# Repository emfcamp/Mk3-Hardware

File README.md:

Hardware
========

Hardware for the TiLDA MKπ Badge for [Electromagnetic Field
2016](https://www.emfcamp.org).

Key Specs
---------
* [STM32L486VGT6](http://www.st.com/content/st_com/en/products/microcontrollers/stm32-32-bit-arm-cortex-mcus/stm32l4-series/stm32l4x6/stm32l486vg.html):
  80MHz ultra-low-power ARM Cortex M4 microcontroller. 1MB Flash, 128KB
  SRAM, USB2. Micropython compatible.
* [CC3100MOD](http://www.ti.com/product/CC3100MOD) SimpleLink WiFi
  Network Processor.
* [LSM6DS3](http://www.st.com/content/st_com/en/products/mems-and-sensors/inemo-inertial-modules/lsm6ds3.html)
  3D accelerometer/gyro.
* [LIS3MDL](http://www.st.com/content/st_com/en/products/mems-and-sensors/e-compasses/lis3mdl.html)
  3D magnetometer.

License
-------
Copyright Electromagnetic Field Ltd. 2016

This documentation describes Open Hardware and is licensed under the
CERN OHL v. 1.2.  You may redistribute and modify this documentation
under the terms of the CERN OHL v.1.2. (http://ohwr.org/cernohl or the
LICENSE file in this repository). This documentation is distributed
WITHOUT ANY EXPRESS OR IMPLIED WARRANTY, INCLUDING OF MERCHANTABILITY,
SATISFACTORY QUALITY AND FITNESS FOR A PARTICULAR PURPOSE. Please see
the CERN OHL v.1.2 for applicable conditions.

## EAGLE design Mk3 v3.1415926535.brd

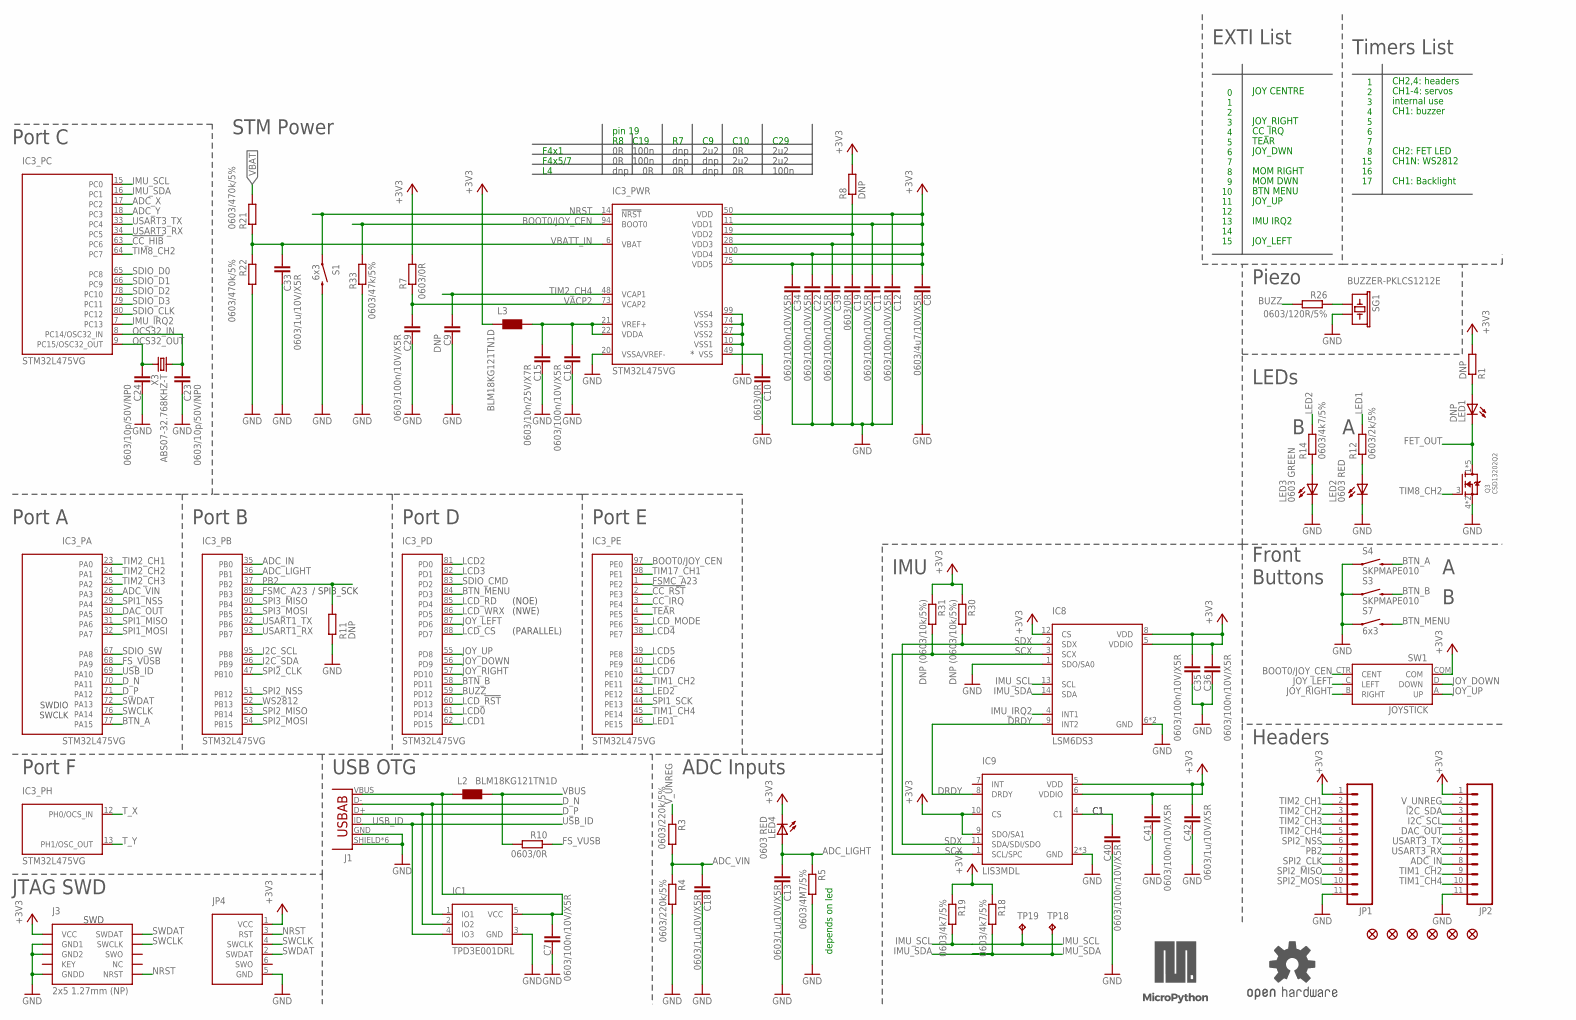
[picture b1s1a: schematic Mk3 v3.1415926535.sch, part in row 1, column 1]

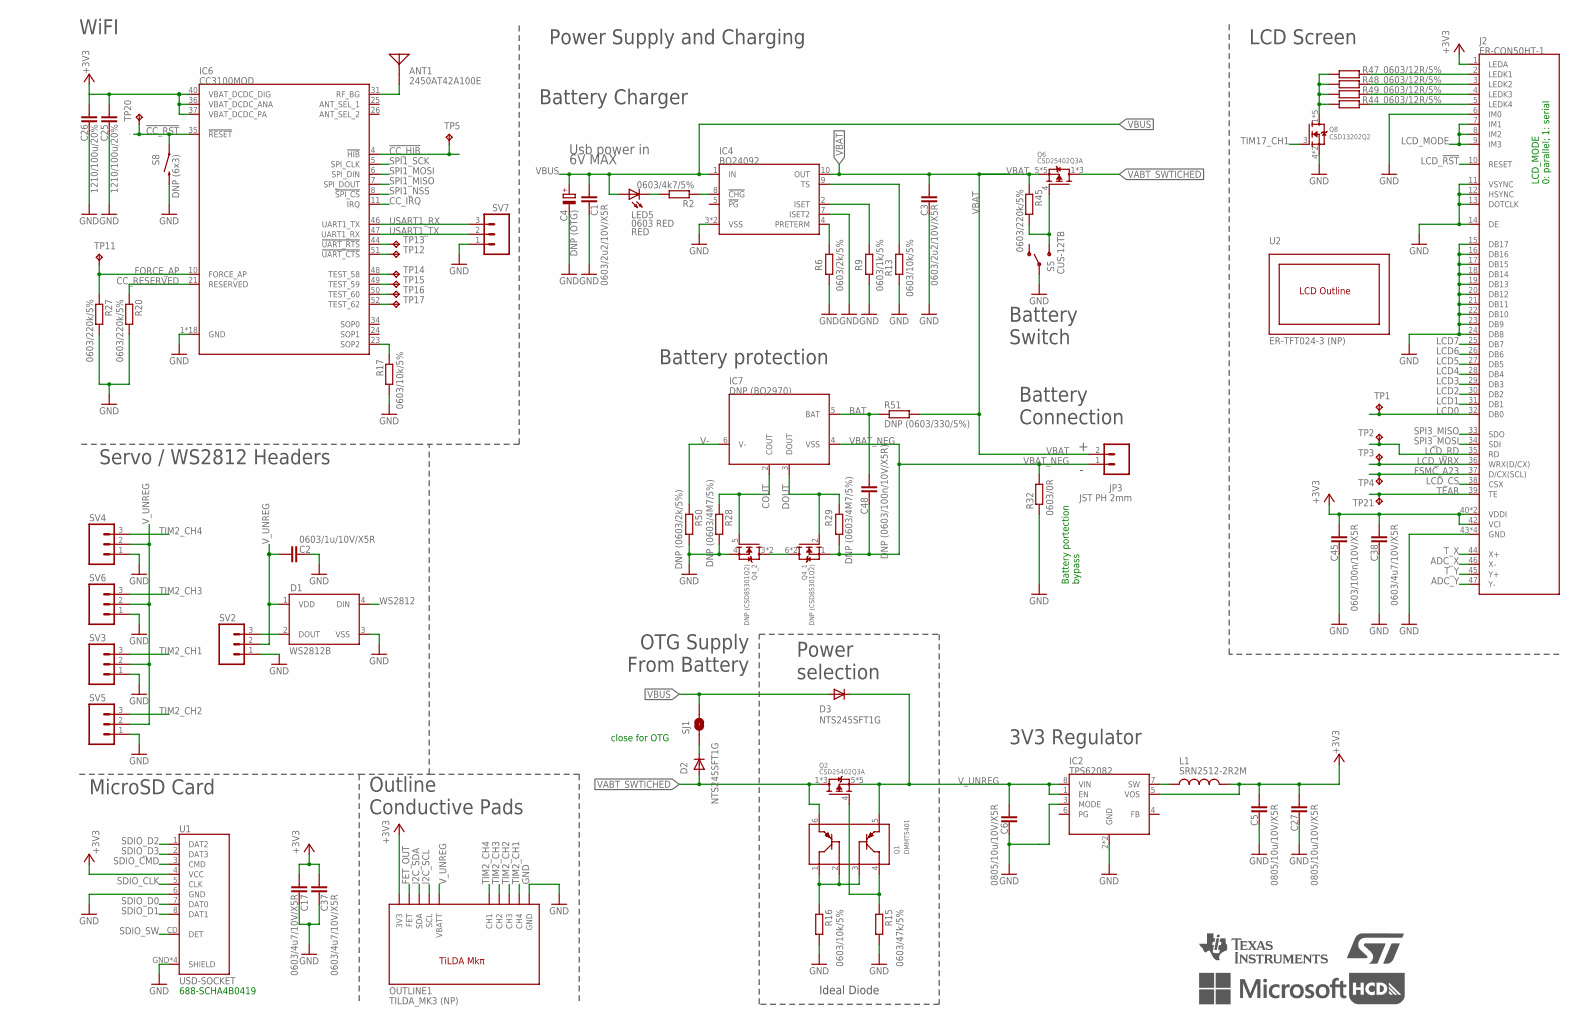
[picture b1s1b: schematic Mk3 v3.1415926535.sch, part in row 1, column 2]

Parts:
ANT1: 2450AT42A100E; 2450AT42A100; FARNELL 2148522
C1, C3: 0603/2u2/10V/X5R; C0603K-SMALL
C2, C13, C18, C33, C42: 0603/1u/10V/X5R; C0603K-SMALL
C4: DNP (OTG); E2,5-6
C5, C6, C27: 0805/10u/10V/X5R; C0805-N
C7, C11, C12, C16, C22, C29, C34, C35, C36, C39, C40, C41, C45: 0603/100n/10V/X5R; C0603K-SMALL
C8, C17, C37, C38: 0603/4u7/10V/X5R; C0603K-SMALL
C9: DNP; C0603K-SMALL
C10, C19: 0603/0R; C0603K-SMALL
C15: 0603/10n/25V/X7R; C0603K-SMALL
C23, C24: 0603/10p/50V/NP0; C0603K-SMALL
C25, C26: 1210/100u/20%; C1210K; FARNELL 1828817
C48: DNP (0603/100n/10V/X5R); C0603K-SMALL
D1: WS2812B
D2, D3: NTS245SFT1G; SOD123
FID1, FID2, FID3, FID4, FID5, FID6: FIDUCIAL1X2.5-STOP; FIDUCIAL-1X2.5-STOP
IC1: TPD3E001DRL; DRL-5; FARNELL 1603422
IC2: TPS62082; WSON8; FARNELL 2064227
IC3: STM32L475VG; TQFP100; FARNELL 2432116
IC4: BQ24092; HVSSOP10; FARNELL 2323723
IC6: CC3100MOD; CC3100MOD-LWK; MOUSER 595-3100MODR11MAMOBR
IC7: DNP (BQ2970); WSON-6; FARNELL 2425793
IC8: LSM6DS3; LGA14; FARNELL 2474253
IC9: LIS3MDL; LGA12; FARNELL 2433083
J1: ZX62-AB-5PA(11); USB-AB-MICRO-SMD_LWK; FARNELL 2293755
J2: ER-CON50HT-1; FH12-50S-0.5SH
J3: 2x5 1.27mm (NP); PINHEAD_2X05_127; FARNELL 1865285
JP1, JP2: (NP); 1X11
JP3: JST PH 2mm; JST-2-SMD; FARNELL 9492615
JP4: (NP); TC2030-MCP-NL
L1: SRN2512-2R2M; 1008; FARNELL 2428203
L2, L3: BLM18KG121TN1D; WUERTH-0805; FARNELL 1781089
LED1: DNP; LED5MM
LED2, LED4, LED5: 0603 RED; LED-0603-CORRECT; FARNELL 2449874
LED3: 0603 GREEN; LED-0603-CORRECT; FARNELL 2426215
LOGO1: OSHW-LOGOM (NP); OSHW-LOGO-M
LOGO2: LOGO_TI-4MM (NP); LOGO_TI_4MM
LOGO3: LOGO_ST-4MM (NP); LOGO_ST_4MM
LOGO4: LOGO_HCD-4MM (NP); LOGO_HDC_4MM
LOGO5: LOGO_MICROSOFT-4MM (NP); LOGO_MS_4MM
LOGO6: LOGO_MICROPYTHON-8MM (NP); LOGO_MICROPYTHON_8MM
OUTLINE1: TILDA_MK3 (NP); TILDA_MKE_OUTLINE
Q1: DMMT5401; SOT26; FARNELL 1773583
Q2, Q6: CSD25402Q3A; Q3A; FARNELL 2501103
Q3, Q8: CSD13202Q2; Q2; FARNELL 2501084
Q4: DNP (CSD85301Q2); Q2_DUAL; FARNELL 2470183
R1: DNP; 0207/10
R2, R14, R18, R19: 0603/4k7/5%; C0603K-SMALL
R3, R4, R20, R27, R45: 0603/220k/5%; C0603K-SMALL
R5: 0603/4M7/5%; C0603K-SMALL
R6, R12: 0603/2k/5%; C0603K-SMALL
R7, R10, R32: 0603/0R; C0603K-SMALL
R8, R11: DNP; C0603K-SMALL
R9: 0603/1k/5%; C0603K-SMALL
R13, R16, R17: 0603/10k/5%; C0603K-SMALL
R15, R33: 0603/47k/5%; C0603K-SMALL
R21, R22: 0603/470k/5%; C0603K-SMALL
R26: 0603/120R/5%; C0603K-SMALL
R28, R29: DNP (0603/4M7/5%); C0603K-SMALL; FARNELL 2059694
R30, R31: DNP (0603/10k/5%); C0603K-SMALL
R44, R47, R48, R49: 0603/12R/5%; C0603K-SMALL; FARNELL 9331280
R50: DNP (0603/2k/5%); C0603K-SMALL
R51: DNP (0603/330/5%); C0603K-SMALL
S1, S7: 6x3; TACTILE-SWITCH-1101NE
S3, S4: SKPMAPE010; SKPMAPE010-COMBINED; FARNELL 1217769
S5: CUS-12TB; SWITCH-SPST-SMD-A; FARNELL 9575146
S8: DNP (6x3); TACTILE-SWITCH-1101NE
SG1: BUZZER-PKLCS1212E
SJ1: OTG (NP); SJ_2S-NO
SV2, SV3, SV4, SV5, SV6, SV7: (NP); 1X03
SW1: JOYSTICK; JOYSTICK_MULTICOMP_NOSILK; FARNELL 1316987
TP1, TP2, TP3, TP4, TP5, TP11, TP12, TP13, TP14, TP15, TP16, TP17, TP18, TP19, TP20, TP21: (NP); B1,27
U1: USD-SOCKET; 0011XAAX09X; FARNELL 2427719
U2: ER-TFT024-3 (NP); ER-TFT024-3
X3: ABS07-32.768KHZ-T; RESONATOR_EPSON_FC_145; FARNELL 2101347

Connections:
!CC_HIB: IC3.63 (PC6), IC6.4 (!HIB), TP5.TP
!CC_RST: IC3.2 (PE3), IC6.35 (!RESET), S8.P$1 (1), TP20.TP
!UART_CTS: IC6.51 (!UART_CTS), TP12.TP
!UART_RTS: IC6.44 (!UART_RTS), TP13.TP
+3V3: C5.1, C8.2, C11.2, C12.2, C17.2, C22.2, C25.1, C26.1, C27.1, C34.2, C35.1, C36.1, C37.2, C38.2, C39.2, C41.1, C42.1, C45.2, IC2.5 (VOS), IC3.11 (VDD1), IC3.28 (VDD3), IC3.50 (VDD), IC3.75 (VDD5), IC3.100 (VDD4), IC6.36 (VBAT_DCDC_ANA), IC6.37 (VBAT_DCDC_PA), IC6.40 (VBAT_DCDC_DIG), IC8.5 (VDDIO), IC8.8 (VDD), IC8.12 (CS), IC9.5 (VDD), IC9.6 (VDDIO), IC9.9 (SDO/SA1), IC9.10 (CS), J2.1 (LEDA), J2.40 (VDDI), J2.41 (VDDI), J2.42 (VCI), J3.1 (VCC), JP1.1, JP2.1, JP4.1 (VCC), L1.2, L3.1, LED4.C, OUTLINE1.3V3, R1.2, R7.1, R8.2, R18.1, R19.1, R30.1, R31.1, SW1.COM, U1.4 (VCC)
ADC_IN: IC3.35 (PB0), JP2.8
ADC_LIGHT: C13.2, IC3.36 (PB1), LED4.A, R5.1
ADC_VIN: C18.2, IC3.26 (PA3), R3.2, R4.1
ADC_X: IC3.17 (PC2), J2.46 (X-)
ADC_Y: IC3.18 (PC3), J2.47 (Y-)
BAT: C48.2, IC7.5 (BAT), R51.1
BOOT0/JOY_CEN: IC3.94 (BOOT0), IC3.97 (PE0), R33.2, SW1.CTR (CENT)
BTN_A: IC3.77 (PA15), S4.2, S4.B1 (2), S4.B2 (2)
BTN_B: IC3.58 (PD11), S3.2, S3.B1 (2), S3.B2 (2)
BTN_MENU: IC3.84 (PD3), S7.P$2 (2)
BUZZ: IC3.59 (PD12), R26.2
C1: C40.1, IC9.4 (C1)
CC_IRQ: IC3.3 (PE4), IC6.11 (IRQ)
CC_RESERVED: IC6.21 (RESERVED), R20.1
COUT: IC7.2 (COUT), Q4.5 (G), R28.1
DAC_OUT: IC3.30 (PA5), JP2.5
DFGFDG: C15.2, C16.2, IC3.21 (VREF+), IC3.22 (VDDA), L3.2
DOUT: IC7.3 (DOUT), Q4.2 (G), R29.1
DRDY: IC8.9 (INT2), IC9.8 (DRDY)
D_N: IC1.1 (IO1), IC3.70 (PA11), J1.D-
D_P: IC1.2 (IO2), IC3.71 (PA12), J1.D+
FET_OUT: LED1.K (C), OUTLINE1.FET, Q3.1 (D), Q3.2 (D), Q3.5 (D), Q3.6 (D), Q3.EP1 (D)
FORCE_AP: IC6.10 (FORCE_AP), R27.1, TP11.TP
FSMC_A23: IC3.1 (PE2), IC3.89 (PB3), J2.37 (D/CX(SCL)), TP4.TP
FS_VUSB: IC3.68 (PA9), R10.1
GND: C1.1, C2.1, C3.1, C4.-, C5.2, C6.2, C7.1, C8.1, C9.1, C10.1, C11.1, C12.1, C13.1, C15.1, C16.1, C17.1, C18.1, C19.1, C22.1, C23.1, C24.1, C25.2, C26.2, C27.2, C29.1, C33.1, C34.1, C35.2, C36.2, C37.1, C38.1, C39.1, C40.2, C41.2, C42.2, C45.1, D1.3 (VSS), IC1.3 (GND), IC2.2 (GND), IC2.3 (MODE), IC2.EP (GND), IC3.10 (VSS1), IC3.20 (VSSA/VREF-), IC3.27 (VSS2), IC3.74 (VSS3), IC3.99 (VSS4), IC4.3 (VSS), IC4.7 (ISET2), IC4.EP (VSS), IC6.1 (GND), IC6.2 (GND), IC6.16 (GND), IC6.27 (GND), IC6.28 (GND), IC6.30 (GND), IC6.32 (GND), IC6.38 (GND), IC6.43 (GND), IC6.55 (GND), IC6.56 (GND), IC6.57 (GND), IC6.58 (GND), IC6.59 (GND), IC6.60 (GND), IC6.61 (GND), IC6.62 (GND), IC6.63 (GND), IC8.1 (SDO/SA0), IC8.6 (GND), IC8.7 (GND), IC9.2 (GND), IC9.3 (GND), IC9.12 (GND), J1.GND, J1.SHIELD, J1.SHIELD@0 (SHIELD), J1.SHIELD@1 (SHIELD), J1.SHIELD@2 (SHIELD), J1.SHIELD@3 (SHIELD), J1.SHIELD@5 (SHIELD), J2.6 (IM0), J2.11 (VSYNC), J2.12 (HSYNC), J2.13 (DOTCLK), J2.14 (DE), J2.15 (DB17), J2.16 (DB16), J2.17 (DB15), J2.18 (DB14), J2.19 (DB13), J2.20 (DB12), J2.21 (DB11), J2.22 (DB10), J2.23 (DB9), J2.24 (DB8), J2.43 (GND), J2.48 (GND), J2.49 (GND), J2.50 (GND), J3.3 (GND1), J3.5 (GND2), J3.9 (GNDD), JP1.11, JP2.11, JP4.5 (GND), LED2.C, LED3.C, OUTLINE1.GND, Q3.4 (S), Q3.EP2 (S), Q4.4 (S), Q8.4 (S), Q8.EP2 (S), R4.2, R5.2, R6.2, R9.2, R11.1, R13.2, R15.2, R16.2, R17.2, R20.2, R22.2, R27.2, R28.2, R32.1, R33.1, R50.2, S1.P$2 (2), S3.1, S3.A1 (1), S3.A2 (1), S4.1, S4.A1 (1), S4.A2 (1), S5.2, S7.P$1 (1), S8.P$2 (2), SG1.P$2 (2), SV2.1, SV3.1, SV4.1, SV5.1, SV6.1, SV7.1, U1.6 (GND), U1.GND (SHIELD), U1.GND1 (SHIELD), U1.GND2 (SHIELD), U1.GND3 (SHIELD)
I2C_SCL: IC3.95 (PB8), JP2.4, OUTLINE1.SCL
I2C_SDA: IC3.96 (PB9), JP2.3, OUTLINE1.SDA
IMU_IRQ2: IC3.7 (PC13), IC8.4 (INT1)
IMU_SCL: IC3.15 (PC0), IC8.13 (SCL), R19.2, TP19.TP
IMU_SDA: IC3.16 (PC1), IC8.14 (SDA), R18.2, TP18.TP
JOY_DOWN: IC3.56 (PD9), SW1.D (DOWN)
JOY_LEFT: IC3.87 (PD6), SW1.C (LEFT)
JOY_RIGHT: IC3.57 (PD10), SW1.B (RIGHT)
JOY_UP: IC3.55 (PD8), SW1.A (UP)
LCD0: IC3.61 (PD14), J2.32 (DB0), TP1.TP
LCD1: IC3.62 (PD15), J2.31 (DB1)
LCD2: IC3.81 (PD0), J2.30 (DB2)
LCD3: IC3.82 (PD1), J2.29 (DB3)
LCD4: IC3.38 (PE7), J2.28 (DB4)
LCD5: IC3.39 (PE8), J2.27 (DB5)
LCD6: IC3.40 (PE9), J2.26 (DB6)
LCD7: IC3.41 (PE10), J2.25 (DB7)
LCD_!RST: IC3.60 (PD13), J2.10 (RESET)
LCD_CS: IC3.88 (PD7), J2.38 (CSX)
LCD_MODE: IC3.5 (PE6), J2.7 (IM1), J2.8 (IM2), J2.9 (IM3)
LCD_RD: IC3.85 (PD4), J2.35 (RD), TP2.TP
LCD_WRX: IC3.86 (PD5), J2.36 (WRX(D/CX)), TP3.TP
LED1: IC3.46 (PE15), R12.2
LED2: IC3.43 (PE12), R14.2
LEDK1: J2.2 (LEDK1), R47.2
LEDK2: J2.3 (LEDK2), R48.2
LEDK3: J2.4 (LEDK3), R49.2
LEDK4: J2.5 (LEDK4), R44.2
unnamed: Q4.3 (D), Q4.6 (D), Q4.EP1 (D), Q4.EP2 (D)
unnamed: R26.1, SG1.P$1 (1)
unnamed: C19.2, IC3.19 (VDD2), R8.1
unnamed: Q1.4 (C2), Q2.4 (G), R15.1
unnamed: Q1.1 (C1), Q1.2 (B1), Q1.3 (B2), R16.1
unnamed: LED5.C, R2.2
unnamed: IC4.8 (!CHG), R2.1
unnamed: IC4.4 (PRETERM), R6.1
unnamed: IC4.2 (ISET), R9.1
unnamed: IC4.9 (TS), R13.1
unnamed: D1.2 (DOUT), SV2.3
unnamed: C7.2, IC1.5 (VCC), J1.VBUS, L2.1
unnamed: D2.C, SJ1.1
unnamed: ANT1.P$1, IC6.31 (RF_BG)
unnamed: C10.2, IC3.49 (VSS)
unnamed: LED3.A, R14.1
unnamed: LED2.A, R12.1
unnamed: LED1.A, R1.1
unnamed: Q8.1 (D), Q8.2 (D), Q8.5 (D), Q8.6 (D), Q8.EP1 (D), R44.1, R47.1, R48.1, R49.1
NRST: IC3.14 (!NRST), J3.10 (NRST), JP4.3 (RST), S1.P$1 (1)
OCS32_IN: C23.2, IC3.8 (PC14/OSC32_IN), X3.P$1 (1)
OCS32_OUT: C24.2, IC3.9 (PC15/OSC32_OUT), X3.P$2 (2)
PB2: IC3.37 (PB2), JP1.7, R11.2
SCX: IC8.3 (SCX), IC9.1 (SCL/SPC), R31.2
SDIO_CLK: IC3.80 (PC12), U1.5 (CLK)
SDIO_CMD: IC3.83 (PD2), U1.3 (CMD)
SDIO_D0: IC3.65 (PC8), U1.7 (DAT0)
SDIO_D1: IC3.66 (PC9), U1.8 (DAT1)
SDIO_D2: IC3.78 (PC10), U1.1 (DAT2)
SDIO_D3: IC3.79 (PC11), U1.2 (DAT3)
SDIO_SW: IC3.67 (PA8), U1.CD (DET)
SDX: IC8.2 (SDX), IC9.11 (SDA/SDI/SDO), R30.2
SOP2: IC6.23 (SOP2), R17.1
SPI1_MISO: IC3.31 (PA6), IC6.7 (SPI_DOUT)
SPI1_MOSI: IC3.32 (PA7), IC6.6 (SPI_DIN)
SPI1_NSS: IC3.29 (PA4), IC6.8 (!SPI_CS)
SPI1_SCK: IC3.44 (PE13), IC6.5 (SPI_CLK)
SPI2_CLK: IC3.47 (PB10), JP1.8
SPI2_MISO: IC3.53 (PB14), JP1.9
SPI2_MOSI: IC3.54 (PB15), JP1.10
SPI2_NSS: IC3.51 (PB12), JP1.6
SPI3_MISO: IC3.90 (PB4), J2.33 (SDO)
SPI3_MOSI: IC3.91 (PB5), J2.34 (SDI)
SW: IC2.7 (SW), L1.1
SWCLK: IC3.76 (PA14), J3.4 (SWCLK), JP4.4 (SWCLK)
SWDAT: IC3.72 (PA13), J3.2 (SWDAT), JP4.2 (SWDAT)
TEAR: IC3.4 (PE5), J2.39 (TE), TP21.TP
TEST_58: IC6.48 (TEST_58), TP14.TP
TEST_59: IC6.49 (TEST_59), TP15.TP
TEST_60: IC6.50 (TEST_60), TP16.TP
TEST_62: IC6.52 (TEST_62), TP17.TP
TIM1_CH2: IC3.42 (PE11), JP2.9
TIM1_CH4: IC3.45 (PE14), JP2.10
TIM2_CH1: IC3.23 (PA0), JP1.2, OUTLINE1.CH4, SV3.3
TIM2_CH2: IC3.24 (PA1), JP1.3, OUTLINE1.CH3, SV5.3
TIM2_CH3: IC3.25 (PA2), JP1.4, OUTLINE1.CH2, SV6.3
TIM2_CH4: C9.2, IC3.48 (VCAP1), JP1.5, OUTLINE1.CH1, SV4.3
TIM8_CH2: IC3.64 (PC7), Q3.3 (G)
TIM17_CH1: IC3.98 (PE1), Q8.3 (G)
T_X: IC3.12 (PH0/OCS_IN), J2.44 (X+)
T_Y: IC3.13 (PH1/OSC_OUT), J2.45 (Y+)
USART1_RX: IC3.93 (PB7), IC6.46 (UART1_TX), SV7.3
USART1_TX: IC3.92 (PB6), IC6.47 (UART1_RX), SV7.2
USART3_RX: IC3.34 (PC5), JP2.7
USART3_TX: IC3.33 (PC4), JP2.6
USB_ID: IC1.4 (IO3), IC3.69 (PA10), J1.ID (USBID)
V-: IC7.6 (V-), R50.1
VABT_SWTICHED: D2.A, Q1.6 (E1), Q2.1 (D), Q2.2 (D), Q2.3 (D), Q6.1 (D), Q6.2 (D), Q6.3 (D)
VACP2: C29.2, IC3.73 (VCAP2), R7.2
VBAT: C3.2, IC4.10 (OUT), JP3.2, Q6.5 (S), Q6.6 (S), Q6.7 (S), Q6.8 (S), Q6.EP (S), R21.2, R45.1, R51.2
VBATT_IN: C33.2, IC3.6 (VBAT), R21.1, R22.1
VBAT_NEG: C48.1, IC7.4 (VSS), JP3.1, Q4.1 (S), R29.2, R32.2
VBAT_SWITCH_CONTROL: Q6.4 (G), R45.2, S5.3 (S)
VBUS: C1.2, C4.+, D3.A, IC4.1 (IN), L2.2, LED5.A, R10.2, SJ1.2
V_UNREG: C2.2, C6.1, D1.1 (VDD), D3.C, IC2.1 (EN), IC2.8 (VIN), JP2.2, OUTLINE1.VBATT, Q1.5 (E2), Q2.5 (S), Q2.6 (S), Q2.7 (S), Q2.8 (S), Q2.EP (S), R3.1, SV2.2, SV3.2, SV4.2, SV5.2, SV6.2
WS2812: D1.4 (DIN), IC3.52 (PB13)

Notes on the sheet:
Headers
LCD Screen
STM Power
Port F
JTAG SWD
Port A
Port B
Port C
Port D
close for OTG
depends on led
MicroSD Card
Servo / WS2812 Headers
Port E
USB OTG
Battery Charger
LEDs
ADC Inputs
LCD_MODE 0: parallel; 1: serial
(PARALLEL)
(NOE)
(NWE)
688-SCHA4B0419
F4x1
F4x5/7
C19
pin 19
dnp
100n
2u2
C10
EXTI List
0 1 2 3 4 5 6 7 8 9 10 11 12 13 14 15
JOY CENTRE
TEAR
JOY_RIGHT
CC_IRQ
JOY_DWN
MOM RIGHT
MOM DWN

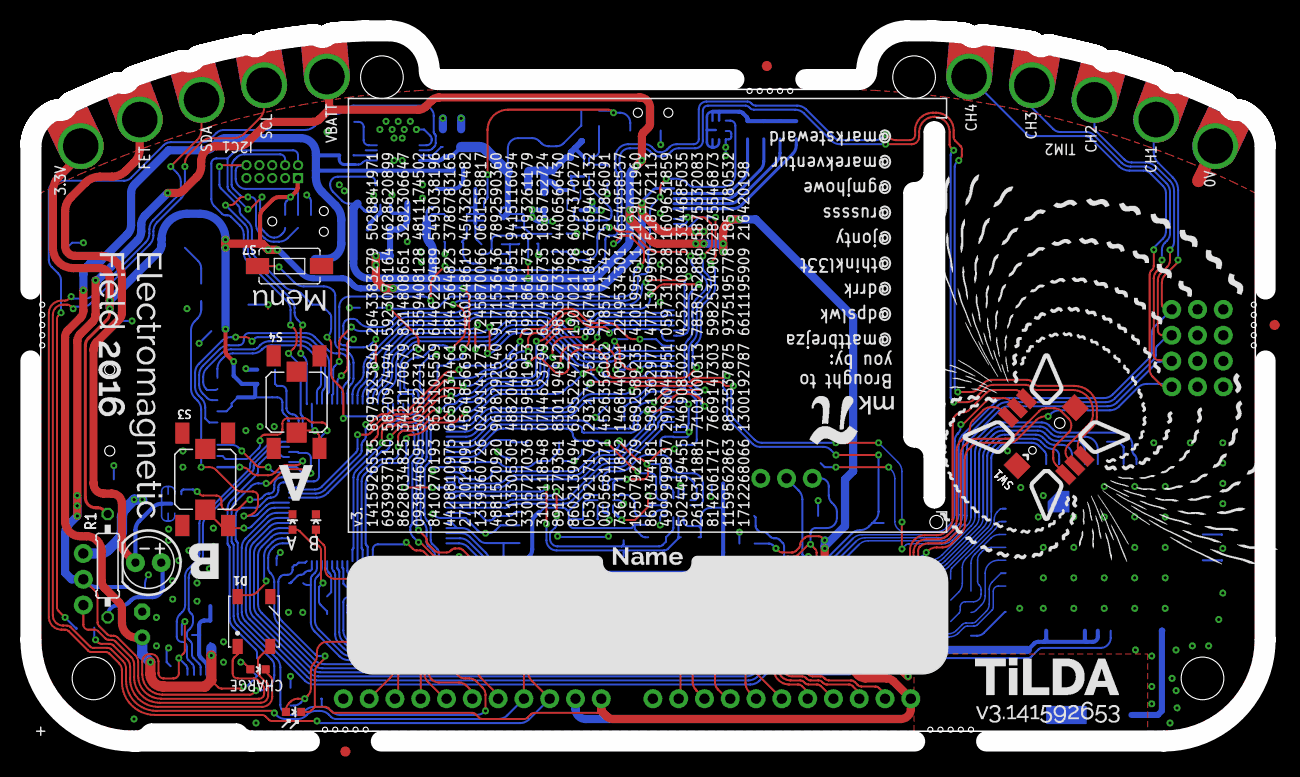
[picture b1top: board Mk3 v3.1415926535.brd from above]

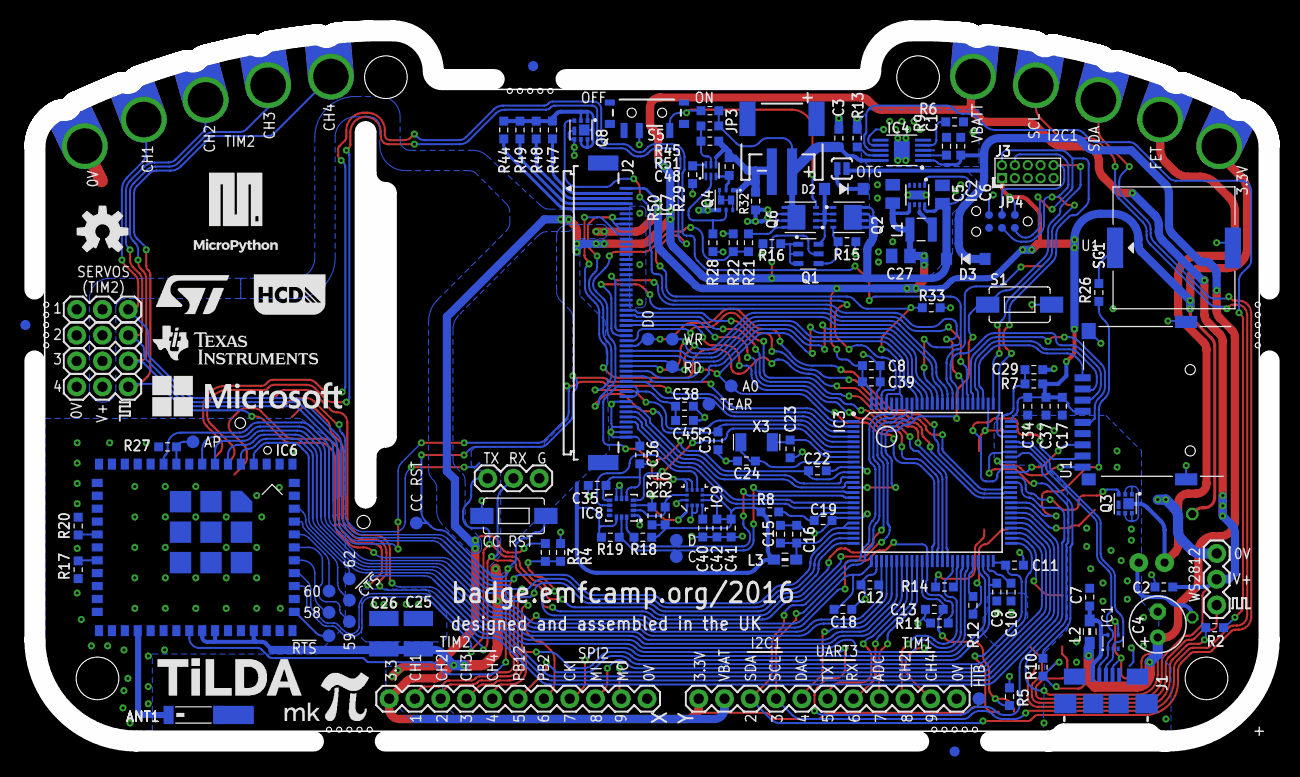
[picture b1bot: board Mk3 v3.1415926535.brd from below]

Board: 2 copper layers, 121.6 x 70.0 mm, 156 parts (139 on the bottom side), 135 nets.

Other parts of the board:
ARTWORK1: ARTWORK_MKπ_BACK; TILDA_MKπ_ARTWORK_BACK
ARTWORK2: ARTWORK_MKπ_FRONT; TILDA_MKπ_ARTWORK_FRONT

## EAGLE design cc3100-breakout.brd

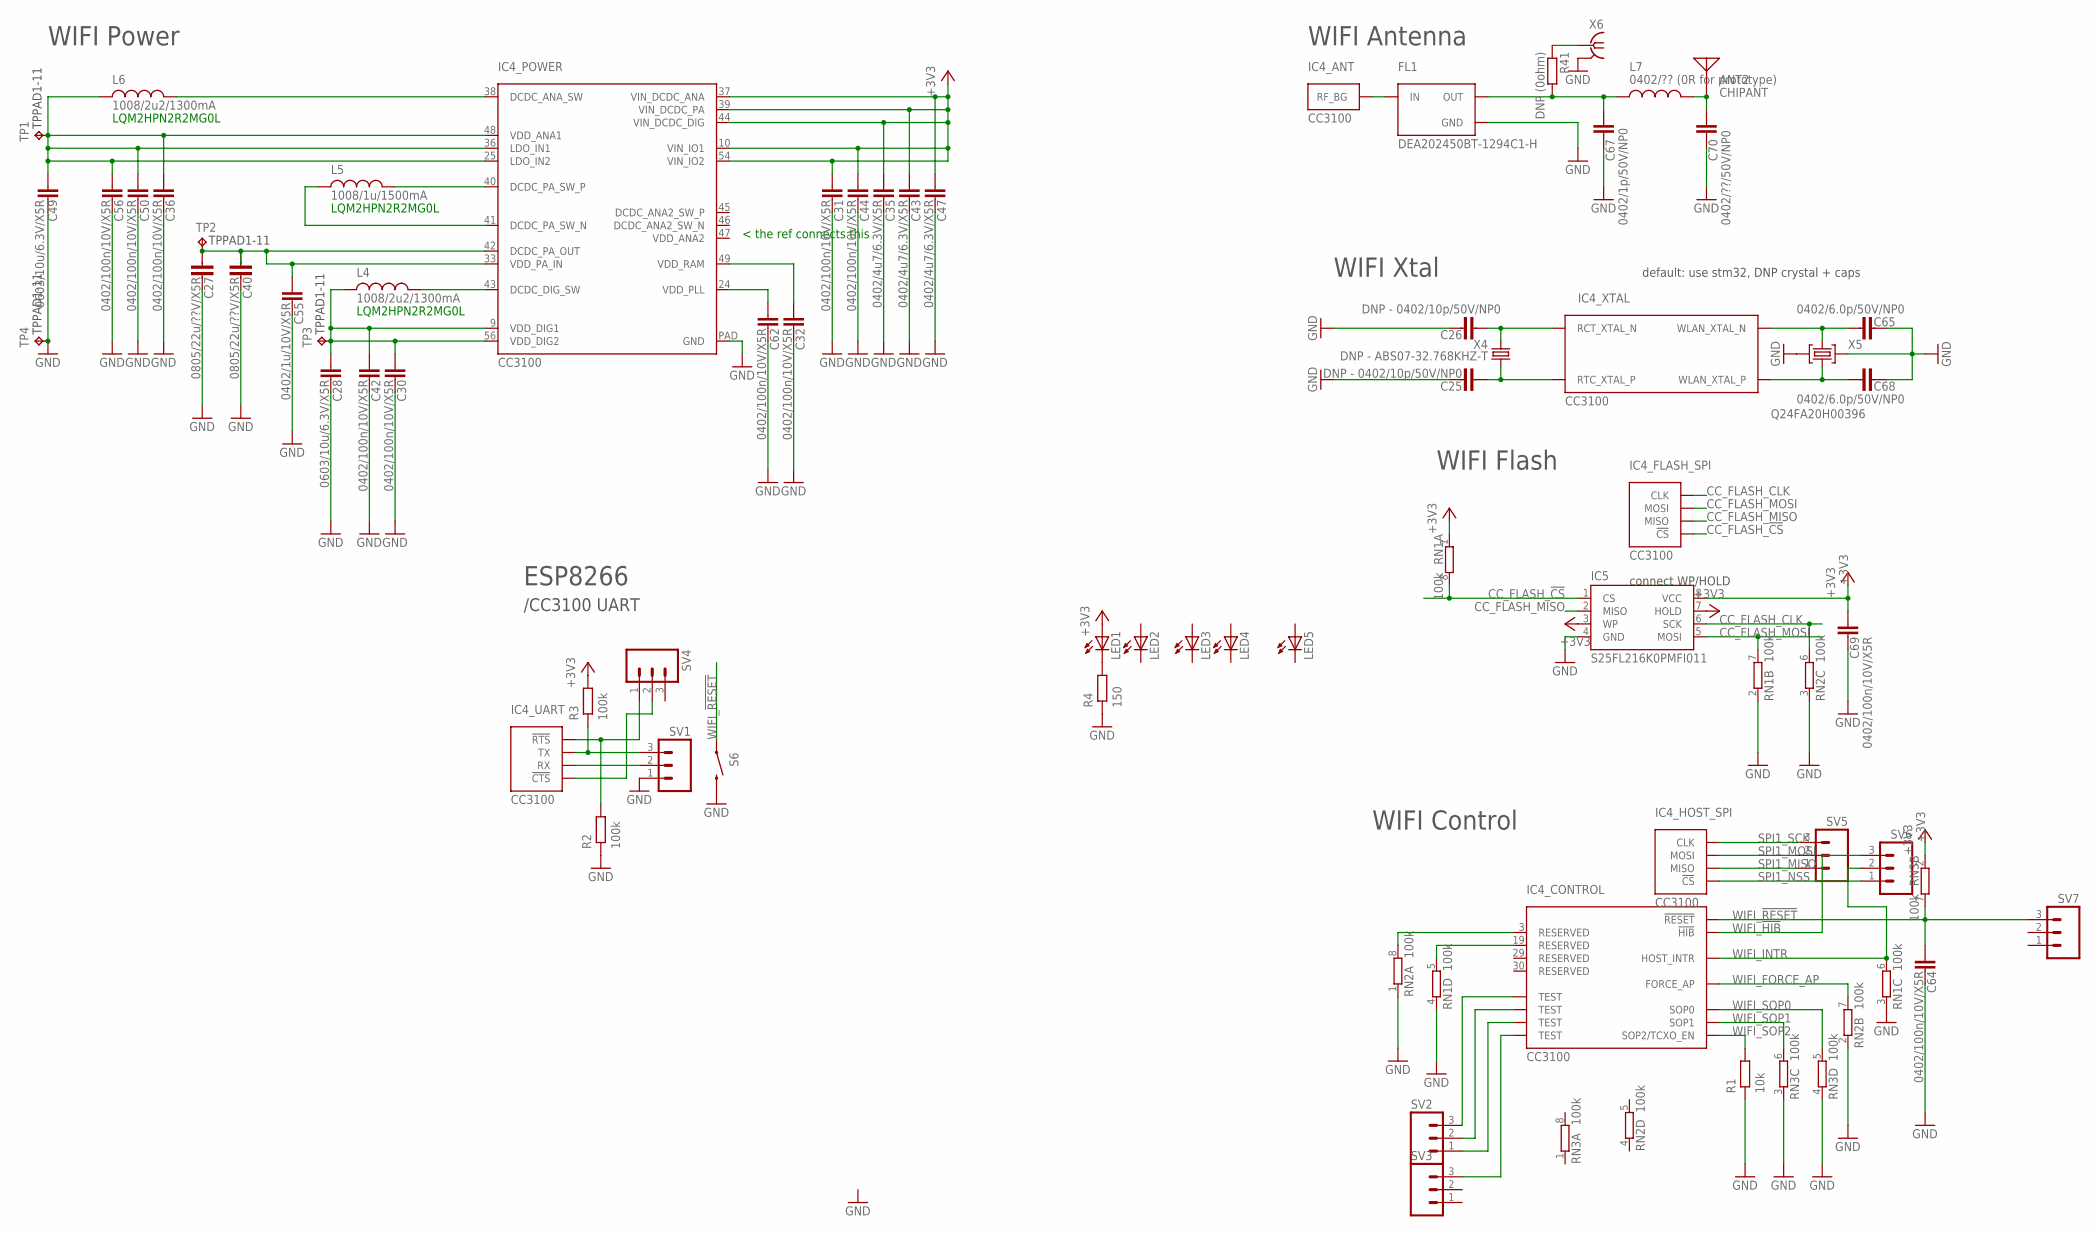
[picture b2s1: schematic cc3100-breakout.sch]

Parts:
ANT2: CHIPANT; 2450AT42A100
C25, C26: DNP - 0402/10p/50V/NP0; C0603-N
C27, C40: 0805/22u/??V/X5R; C0805-N
C28, C49: 0603/10u/6.3V/X5R; C0603K-SMALL
C30, C31, C32, C36, C42, C44, C50, C56, C62, C64, C69: 0402/100n/10V/X5R; C0402-SMALLER
C35, C43, C47: 0402/4u7/6.3V/X5R; C0402-SMALLER
C55: 0402/1u/10V/X5R; C0402-SMALLER
C65, C68: 0402/6.0p/50V/NP0; C0603-N
C67: 0402/1p/50V/NP0; C0402-SMALLER
C70: 0402/??/50V/NP0; C0402-SMALLER
FL1: DEA202450BT-1294C1-H; DEA202450BT
IC4: CC3100; VQFN-64
IC5: S25FL216K0PMFI011; SO08-EIAJ
L4, L6: 1008/2u2/1300mA; 1008
L5: 1008/1u/1500mA; 1008
L7: 0402/?? (0R for prototype); L0402
LED1, LED2, LED3, LED4, LED5: LEDCHIPLED_0603; CHIPLED_0603
R1: 10k; R0603-N
R2, R3: 100k; R0603-N
R4: 150; R0603-N
R41: DNP (0ohm); R0402-SMALLER
RN1, RN2, RN3: 100k; EXB38V
S6: SWITCH-MOMENTARY-2SMD-1101NE; TACTILE-SWITCH-1101NE
SV1, SV2, SV3, SV4, SV5, SV6, SV7: M03PTH; 1X03
TP1, TP2, TP3, TP4: TPPAD1-11; P1-11
X4: DNP - ABS07-32.768KHZ-T; RESONATOR_EPSON_FC_145
X5: Q24FA20H00396; CRYSTAL-2.5X2.0
X6: MC-921

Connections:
+3V3: C31.2, C35.2, C43.2, C44.2, C47.2, C69.2, IC4.10 (VIN_IO1), IC4.37 (VIN_DCDC_ANA), IC4.39 (VIN_DCDC_PA), IC4.44 (VIN_DCDC_DIG), IC4.54 (VIN_IO2), IC5.3 (WP), IC5.7 (HOLD), IC5.8 (VCC), LED1.A, R3.2, RN1.1, RN3.2 (1)
ANT: ANT2.P$1, C70.1, L7.2
CC_FLASH_!CS: IC4.14 (!CS), IC5.1 (CS), RN1.8 (2)
CC_FLASH_CLK: IC4.11 (CLK), IC5.6 (SCK), RN2.6 (2)
CC_FLASH_MISO: IC4.13 (MISO), IC5.2 (MISO)
CC_FLASH_MOSI: IC4.12 (MOSI), IC5.5 (MOSI), RN1.7 (2)
GND: C25.1, C26.1, C27.1, C28.1, C30.1, C31.1, C32.1, C35.1, C36.1, C40.1, C42.1, C43.1, C44.1, C47.1, C49.1, C50.1, C55.1, C56.1, C62.1, C64.1, C65.1, C67.2, C68.1, C69.1, C70.2, FL1.GND@2 (GND), FL1.GND@4 (GND), IC4.PAD (GND), IC5.4 (GND), R1.1, R2.1, R4.1, RN1.2 (1), RN1.3 (1), RN1.4 (1), RN2.1, RN2.2 (1), RN2.3 (1), RN3.3 (1), RN3.4 (1), S6.2, SV1.1, TP4.TP, X5.2 (GND), X5.4 (GND), X6.2@1 (GND), X6.2@2 (GND)
unnamed: IC4.50 (!RTS), R2.2, SV4.1
unnamed: C67.1, FL1.OUT, L7.1, R41.2
unnamed: FL1.IN, IC4.31 (RF_BG)
unnamed: IC4.58 (TEST), SV2.3
unnamed: C26.2, IC4.52 (RCT_XTAL_N), X4.P$1 (1)
unnamed: IC4.59 (TEST), SV2.2
unnamed: IC4.60 (TEST), SV2.1
unnamed: C65.2, IC4.22 (WLAN_XTAL_N), X5.3 (C2)
unnamed: C68.2, IC4.23 (WLAN_XTAL_P), X5.1 (C1)
unnamed: IC4.3 (RESERVED), RN2.8 (2)
unnamed: IC4.19 (RESERVED), RN1.5 (2)
unnamed: IC4.62 (TEST), SV3.3
unnamed: IC4.61 (!CTS), SV4.2
unnamed: LED1.C, R4.2
unnamed: IC4.38 (DCDC_ANA_SW), L6.2
unnamed: C27.2, C40.2, C55.2, IC4.33 (VDD_PA_IN), IC4.42 (DCDC_PA_OUT), TP2.TP
unnamed: C36.2, C49.2, C50.2, C56.2, IC4.25 (LDO_IN2), IC4.36 (LDO_IN1), IC4.48 (VDD_ANA1), L6.1, TP1.TP
unnamed: IC4.43 (DCDC_DIG_SW), L4.2
unnamed: C62.2, IC4.24 (VDD_PLL)
unnamed: C28.2, C30.2, C42.2, IC4.9 (VDD_DIG1), IC4.56 (VDD_DIG2), L4.1, TP3.TP
unnamed: IC4.40 (DCDC_PA_SW_P), L5.2
unnamed: IC4.41 (DCDC_PA_SW_N), L5.1
unnamed: C32.2, IC4.49 (VDD_RAM)
unnamed: C25.2, IC4.51 (RTC_XTAL_P), X4.P$2 (2)
unnamed: IC4.55 (TX), R3.1, SV1.3
unnamed: R41.1, X6.1
SPI1_MISO: IC4.7 (MISO), SV5.1
SPI1_MOSI: IC4.6 (MOSI), SV5.2
SPI1_NSS: IC4.8 (!CS), SV6.1
SPI1_SCK: IC4.5 (CLK), SV5.3
USART6_TX: IC4.57 (RX), SV1.2
WIFI_!HIB: IC4.2 (!HIB), SV6.3
WIFI_!RESET: C64.2, IC4.32 (!RESET), RN3.7 (2), S6.1, SV7.3
WIFI_FORCE_AP: IC4.4 (FORCE_AP), RN2.7 (2)
WIFI_INTR: IC4.15 (HOST_INTR), RN1.6 (2), SV6.2
WIFI_SOP0: IC4.35 (SOP0), RN3.5 (2)
WIFI_SOP1: IC4.34 (SOP1), RN3.6 (2)
WIFI_SOP2: IC4.21 (SOP2/TCXO_EN), R1.2

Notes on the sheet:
WIFI Antenna
WIFI Flash
WIFI Xtal
LQM2HPN2R2MG0L
WIFI Power
WIFI Control
default: use stm32, DNP crystal + caps
connect WP/HOLD
ESP8266
/CC3100 UART
< the ref connects this

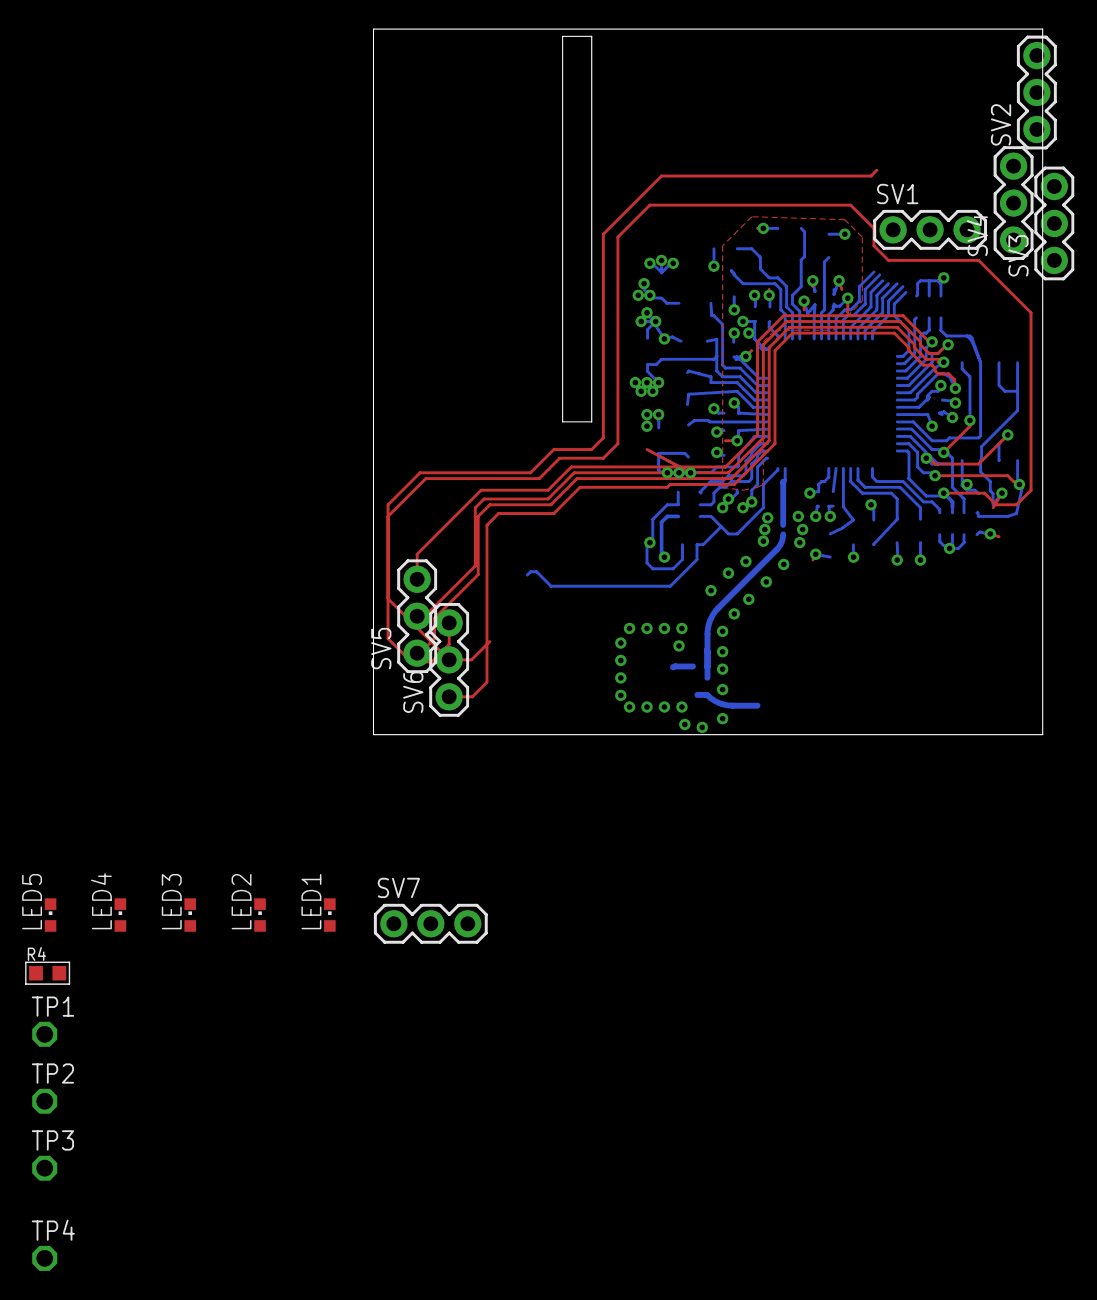
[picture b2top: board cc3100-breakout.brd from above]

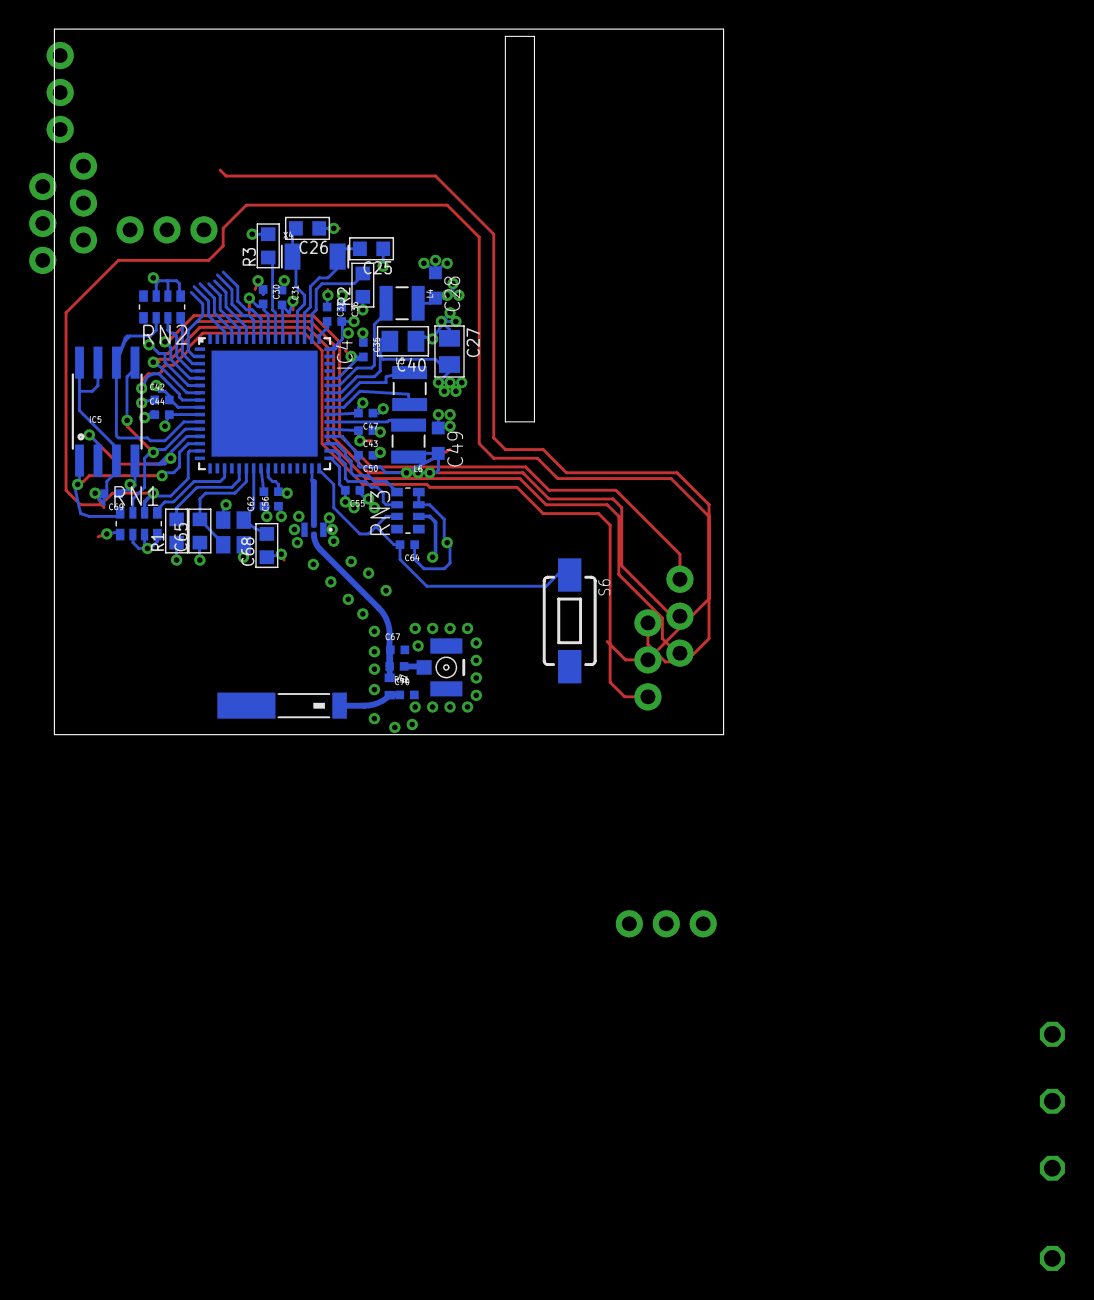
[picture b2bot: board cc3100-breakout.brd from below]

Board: 4 copper layers, 46.0 x 48.5 mm, 61 parts (44 on the bottom side), 45 nets.

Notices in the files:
parts and their libraries:
SparkFun-LED: Licensing: Creative Commons ShareAlike 4.0 International - https://creativecommons.org/licenses/by-sa/4.0
TiLDA Mk3 Parts: ©2009 ROFA.cz - modified and updated by Robert Darlington ‹rdarlington@gmail.com›
